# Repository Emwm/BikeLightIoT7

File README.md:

# 🚲 ESP32 Smart Bike Tracker

An ESP32-based smart tracking and monitoring system for bicycles, combining GNSS (GPS) tracking, motion detection, power management, battery monitoring, and LoRa communication to create an intelligent, low-power system for bike security and telemetry.

---

## 📚 Table of Contents

- [Features](#-features)
- [Getting Started](#-getting-started)
- [Power Modes](#-power-modes)
- [GNSS (GPS) Handler](#-gnss-gps-handler)
- [Motion Detector](#-motion-detector)
- [Light Control](#-light-control)
- [LoRa Communication](#-lora-communication)
- [Battery Monitoring](#-battery-monitoring)
- [Inactivity Handling](#-inactivity-handling)
- [Main Loop Overview](#-main-loop-overview)
- [Modules Summary](#-modules-summary)
- [Contributing](#-contributing)
- [License](#-license)

---

## 📦 Features

- Real-time GPS tracking  
- LoRa communication to send bike data remotely  
- Motion detection using an accelerometer  
- Battery monitoring via MAX17048 fuel gauge  
- Smart power management with 3 modes: ACTIVE, PARK, SLEEP  
- Inactivity-based sleep transitions  
- Wake-up on button press or timer  
- Integrated button and light control  

---

## 🛠️ Getting Started

### ✅ Prerequisites

- PlatformIO or Arduino IDE  
- ESP32 board definitions installed  
- Required libraries:  
  - TinyGPS++  
  - Wire  
  - SPI  

### 🚀 Flashing the Firmware

```bash
git clone https://github.com/youruser/esp32-smart-bike-tracker.git
cd esp32-smart-bike-tracker
# Open with Arduino IDE or PlatformIO and upload to your ESP32
```

---

## 🔘 Button Handler

Manages button input from GPIO 33, used to:
- Wake up the system
- Trigger GPS updates
- Toggle power modes

### ⚙️ Configuration

| Constant        | Description                  |
|----------------|------------------------------|
| `BUTTON_PIN_1` | GPIO pin for Button 1 (GPIO33) |

```cpp
#define BUTTON_PIN_1 33
```

### 📦 Variables

```cpp
extern volatile bool button1Pressed;
extern unsigned long lastActivityTime;
```

### 📋 API

| Function            | Description                              |
|---------------------|------------------------------------------|
| `setupButtons()`    | Initializes GPIOs as `INPUT_PULLDOWN`    |
| `checkButtonPresses()` | Resets flags, updates `lastActivityTime` |

---

## 🧠 Power Modes

System behavior varies by mode:

### 🟢 ACTIVE Mode
- Full GPS + LoRa operation
- Motion detection and lighting enabled
- Auto-exit on inactivity

### 🟡 PARK Mode
- Enters light sleep
- Periodic wake via RTC or button
- Ideal for short-term stationary periods

### 🔴 SLEEP Mode
- Enters deep sleep for max power saving
- Wake on button press only
- Best for long inactivity

---

## 🛰 GNSS (GPS) Handler

Handles GPS data using the TinyGPS++ library. Sends the location everytime the mode of the system changes.

### 📋 API

| Method              | Description                                |
|---------------------|--------------------------------------------|
| `begin()`           | Initializes GPS module                     |
| `update()`          | Feeds serial data to TinyGPS++             |
| `isConnected()`     | Checks for GPS fix (≥4 satellites)         |
| `checkLocation()`   | Returns `GPSPosition` with lat/lon         |

### 📍 Example

This flag is used to update the location and send it.

```cpp
if (sendLocationFlag) {
    GPSPosition pos = gnss.checkLocation();
    // Use pos.latitude, pos.longitude
}
```

---

## 🕹️ Motion Detector

Detects bike movement using a 3-axis accelerometer (e.g. ADXL345).

### 📋 API

| Method                  | Description                                  |
|--------------------------|----------------------------------------------|
| `isMoving()`             | Returns `true` if movement detected          |
| `begin()`                | Initializes the sensor                       |
| `MotionDetector(...)`    | Constructor with I2C address and threshold   |

```cpp
MotionDetector motion(0x53); // ADXL345 default I2C address
```

---

## 💡 Light Control

Uses an LDR + MAX7219 LED matrix to control lights.

### ⚙️ Configuration

| Item               | Pin          |
|--------------------|--------------|
| `LDR_PIN`          | Analog Input |
| `LED_LOW_BAT`      | Digital Output |
| `DIN`              | GPIO 14      |
| `CLK`              | GPIO 13      |
| `CS`               | GPIO 12      |

### 📋 API

| Function                      | Description                               |
|-------------------------------|-------------------------------------------|
| `setupLight()`                | Initializes LED matrix                    |
| `controlLight()`              | Enables/disables display based on LDR     |
| `turnLightoff()`              | Manually disables display                 |
| `manageBatteryWarning(float)`| Activates LED when battery < 25%          |

---

## 📡 LoRaWAN Communication

Handles uplink/downlink communication via RN2483 LoRa module using OTAA.

### 🔧 ESP32 to RN2483 Wiring

| Function | ESP32 Pin |
|----------|-----------|
| TX → RN  | GPIO 19   |
| RX ← RN  | GPIO 18   |
| RESET    | GPIO 23   |

### 📋 API

| Function                                  | Description                         |
|-------------------------------------------|-------------------------------------|
| `init_lora()`                             | Initializes LoRaWAN + joins TTN     |
| `send_lora(devMode, battery, lon, lat)`   | Sends telemetry as CSV string       |
| `recieve_lora()`                          | Reads JSON downlink and parses value|

### 📤 Uplink Format (CSV)

```text
1,3.85,12.34,56.78
```

### 📥 Downlink Format

TTN → JSON string in HEX:

```json
{"value": 2}
```

TTN Payload: `7b2276616c7565223a20327d`

Parsed into `int value = 2`.

---

## 🔋 Battery Monitoring

Powered by the MAX17048 fuel gauge.

```cpp
batterypercentage = battery.percent();
```

Low battery warning is triggered by:

```cpp
manageBatteryWarning(batterypercentage);
```

---

## ⏱️ Inactivity & Mode Handling

Automatically switches to `PARK` mode if idle for 60 seconds:

```cpp
if (millis() - lastActivityTime > 60000) {
    // Switch to PARK
}
```

Button interrupt handler toggles modes:

```cpp
void IRAM_ATTR handleInterrupt1();
```

Transitions:
- `ACTIVE → PARK`
- `PARK → SLEEP`

---

## 🔁 Main Loop Structure

```cpp
switch (getCurrentMode()) {
    case ACTIVE:
        // Motion + LoRa
        break;
    case PARK:
        // Light sleep
        break;
    case SLEEP:
        // Deep sleep
        break;
}
```

---

## 🛠 Modules Summary

| Module         | Description                            |
| -------------- | -------------------------------------- |
| powerModes     | Manages sleep states and wake sources  |
| GNSSHandler    | Handles GPS via GNSS                   |
| MotionDetector | Reads accelerometer to detect movement |
| ESP32\_lora    | Sends and receives data via LoRa       |
| MAX17048       | Monitors battery charge level          |
| buttonHandler  | Detects button presses                 |
| lightControl   | Manages LED or light control           |

## Authors

Group 7 in the DTU course 34346 Networking technologies and application development for IoT

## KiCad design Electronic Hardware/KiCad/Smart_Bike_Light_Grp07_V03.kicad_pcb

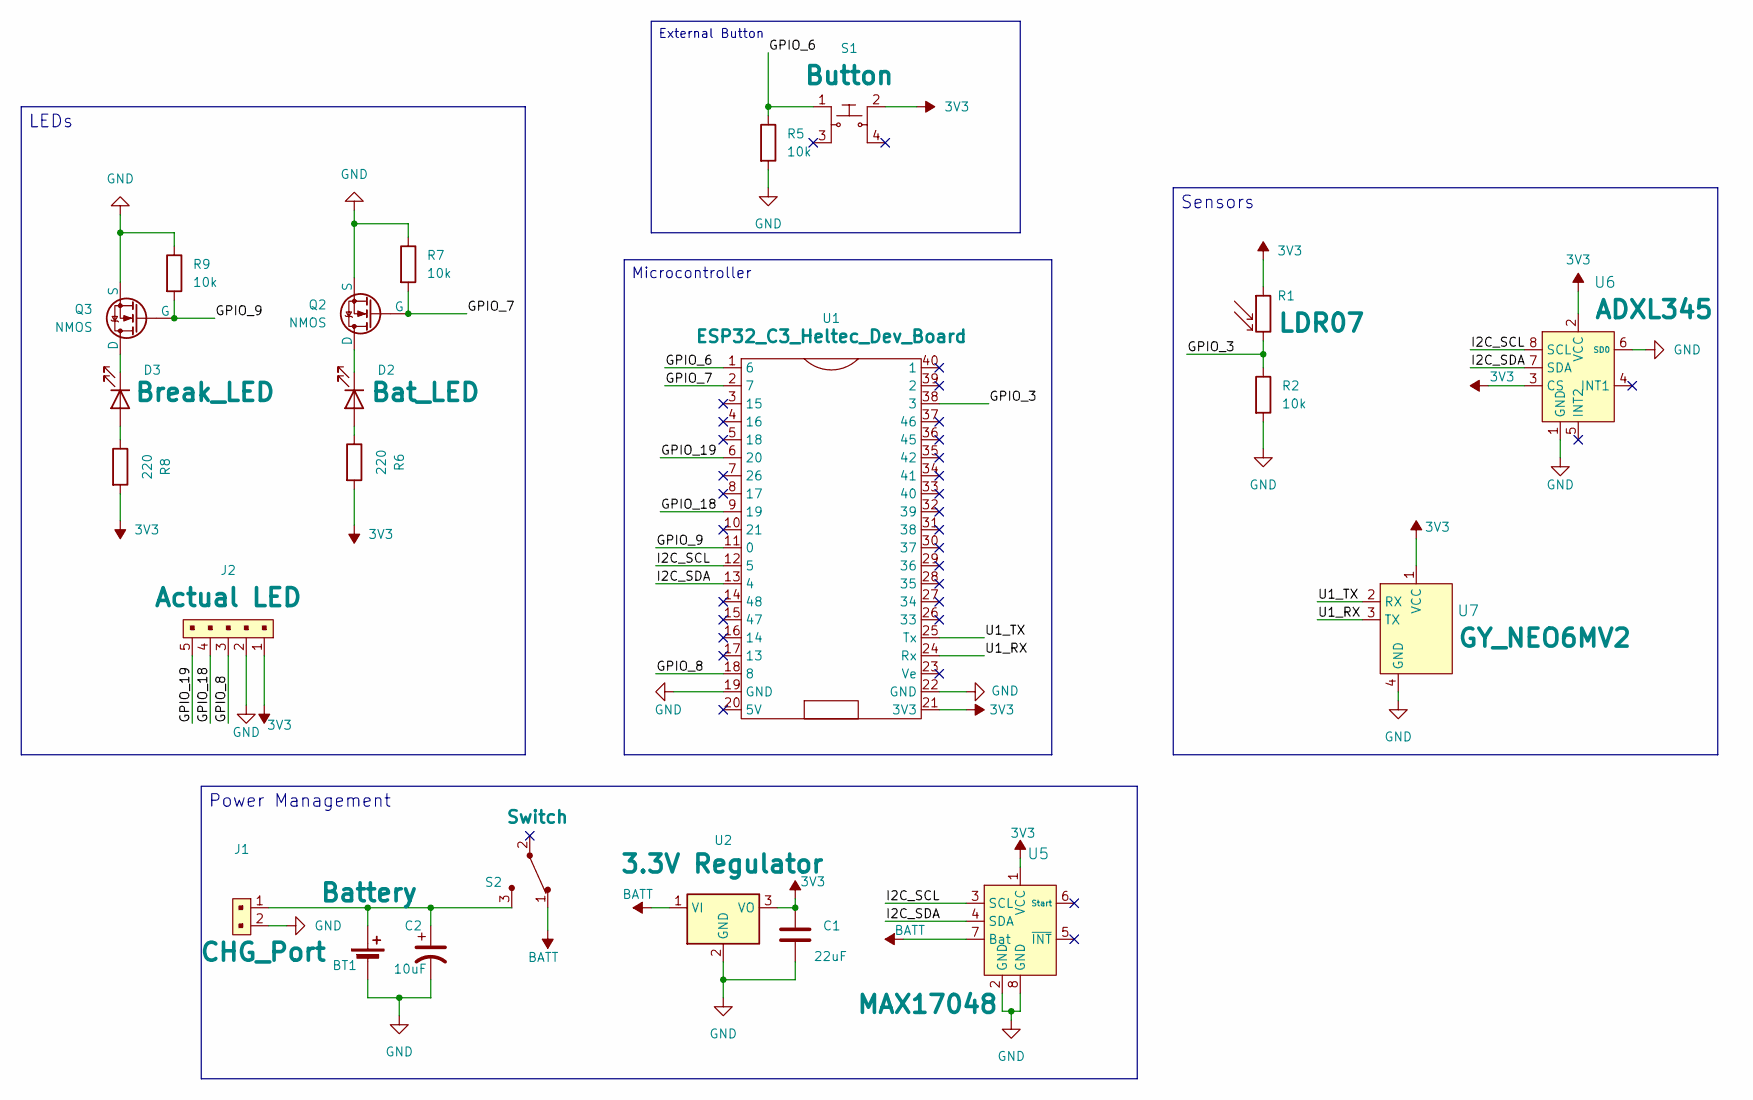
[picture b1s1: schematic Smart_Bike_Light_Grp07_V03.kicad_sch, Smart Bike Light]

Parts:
BT1: Battery; Terminal_Block_D1.3mm_P5mm
C1: 22uF; C_Axial_L3.8mm_D2.6mm_P7.50mm_Horizontal
C2: 10uF; C_Axial_L3.8mm_D2.6mm_P7.50mm_Horizontal
D2: Bat_LED; LED_D3.0mm_Clear
D3: Break_LED; LED_D3.0mm_Clear
J1: CHG_Port; Terminal_Block_D1.3mm_P5mm; MPN 640456-2; Digi-Key_PN A1921-ND
J2: Actual LED; JST_XA_B05B-XASK-1-A_1x05_P2.50mm_Vertical; MPN B5B-XH-A(LF)(SN); Digi-Key_PN 455-2270-ND
Q2, Q3: NMOS; PinHeader_1x3_P2.54_Drill1.1mm
R1: LDR07; R_LDR_5.1x4.3mm_P3.4mm_Vertical
R2, R5, R7, R9: 10k; R_Axial_DIN0204_L3.6mm_D1.6mm_P5.08mm_Horizontal
R6, R8: 220; R_Axial_DIN0204_L3.6mm_D1.6mm_P5.08mm_Horizontal
S1: Button; SW_DIP_SPSTx02_Slide_9.78x7.26mm_W7.62mm_P2.54mm; MPN KS-01Q-01; Digi-Key_PN EG4791-ND
S2: Switch; SW_Slide-03_Wuerth-WS-SLTV_10x2.5x6.4_P2.54mm; MPN EG1218; Digi-Key_PN EG1903-ND
U1: ESP32_C3_Heltec_Dev_Board; DIP-40_W25.4mm
U2: 3.3V Regulator; PinHeader_1x3_P2.54_Drill1.1mm
U5: MAX17048; DIP-8_W7.62mm; MPN MAX44009EDT+T; Digi-Key_PN MAX44009EDT+TCT-ND
U6: ADXL345; DIP-8_W7.62mm; MPN MAX44009EDT+T; Digi-Key_PN MAX44009EDT+TCT-ND
U7: GY_NEO6MV2; DIP-8_W7.62mm; MPN MAX44009EDT+T; Digi-Key_PN MAX44009EDT+TCT-ND

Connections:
-3V3: C1.1, J2.1, R1.1, R6.2, R8.2, S1.2, U1.21 (3V3), U2.3 (VO), U5.1 (VCC), U6.2 (VCC), U6.3 (CS), U7.1 (VCC)
-BATT: S2.1, U2.1 (VI), U5.7 (Bat)
/GPIO_3: R1.2, R2.1, U1.38 (3)
/GPIO_6: R5.1, S1.1, U1.1 (6)
/GPIO_7: Q2.2 (G), R7.2, U1.2 (7)
/GPIO_8: J2.3, U1.18 (8)
/GPIO_9: Q3.2 (G), R9.2, U1.11 (0)
/GPIO_18: J2.4, U1.9 (19)
/GPIO_19: J2.5, U1.6 (20)
/I2C_SCL: U1.12 (5), U5.3 (SCL), U6.8 (SCL)
/I2C_SDA: U1.13 (4), U5.4 (SDA), U6.7 (SDA)
/U1_RX: U1.24 (Rx), U7.3 (TX)
/U1_TX: U1.25 (Tx), U7.2 (RX)
GND: BT1.2 (-), C1.2, C2.2, J1.2, J2.2, Q2.3 (S), Q3.3 (S), R2.2, R5.2, R7.1, R9.1, U1.19 (GND), U1.22 (GND), U2.2 (GND), U5.2 (GND), U5.8 (GND), U6.1 (GND), U6.6 (SD0), U7.4 (GND)
unnamed: BT1.1 (+), C2.1, J1.1, S2.3
unnamed: D2.2 (A), R6.1
unnamed: D2.1 (K), Q2.1 (D)
unnamed: D3.2 (A), R8.1
unnamed: D3.1 (K), Q3.1 (D)

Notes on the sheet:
Power Management
External Button
Microcontroller
LEDs
Sensors

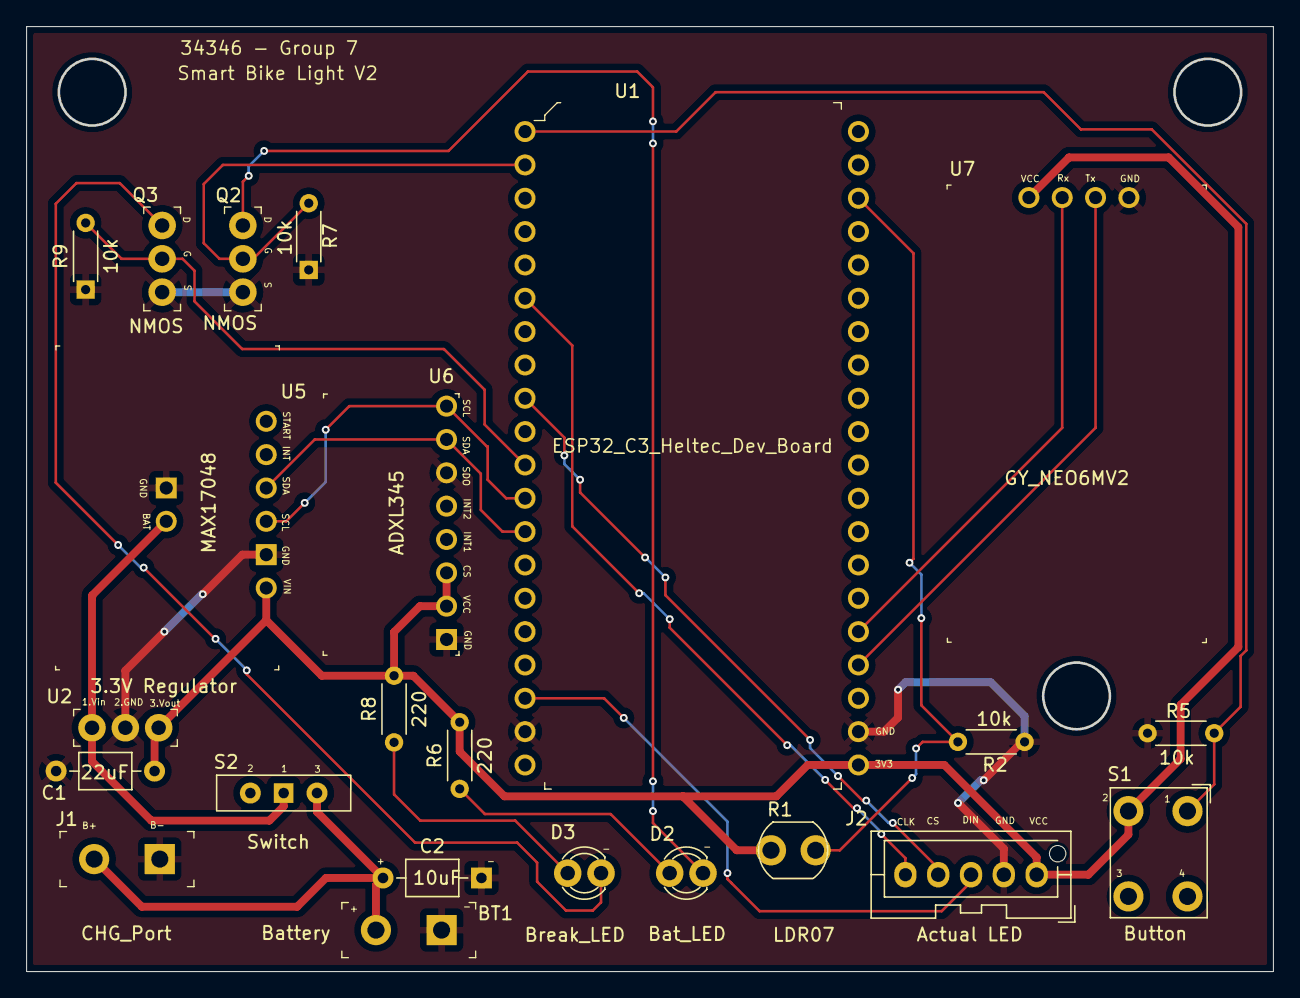
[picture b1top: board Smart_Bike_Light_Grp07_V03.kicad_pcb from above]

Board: 2 copper layers, 95.0 x 72.0 mm, 23 parts (0 on the bottom side), 19 nets.

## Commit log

2025-03-24 Examples Commit
2025-04-03 Sleep Modes and LDR sensor
    I made the sleep modes, the switches between them are not perfect yet, but all of the modes are working as intended. The LDR only turns on the LED, if it is dark and only in the active mode. Also I a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
2025-04-03 just renaming to main file
2025-04-03 Smaller changes of Code
    1. Put the interrupts into the powermodes
    2. Defined the pins in the header to clear a problem
2025-04-03 change the selection of wakeup pins
    Trying to make multiple Pins able to wake up from deep sleep
2025-04-05 Create GNSS.h (Header file)
    Header file for GNSS
2025-04-05 Create GNSS.cpp
    GNSS source file
2025-04-06 Multiple Wakeups ready and correcting some stuff
2025-04-09 Create LoRaWan_v1.ino
    adding the draft of my code for the lorawan
2025-04-24 Updated files for LoraWAN
2025-04-24 update to lora header file
2025-04-27 Added all sensors and the Lorawan code to the project
2025-05-01 Added comments to all the code
2025-05-01 Update LoraWAN_Reese.cpp
    update to lora cpp file
2025-05-01 Updated the code to include batterypercentage
    Just added a function that activates a battery when it is lower then 25% and added the batterychecking
2025-05-08 Update powerModes.cpp
    Just added the fixed code from today, but still have to make the wake up for the light sleep
2025-05-08 Update GNSSHandler.h
    Just to fix the include of the TinyGPSPlus
2025-05-16 ESP32 lorawan
2025-05-16 System working, without lora
2025-05-18 updated lora code
2025-05-18 Close to final version
    Added function for the set of State
2025-05-18 modes updates
2025-05-18 FIxes
2025-05-18 FInished code
2025-05-20 Code final
2025-05-21 Fritzing ESP32 Wroom
2025-05-21 PCB Files Kicad
2025-05-21 Schematic Image
2025-05-21 PCB Layout Image
2025-05-21 Rendered Image PCB
2025-05-21 Gerber File
2025-05-21 All FootPrints
2025-05-24 Update main branch
2025-05-24 Another delete of old files
2025-05-24 Update powerModes.cpp
    Updated code that it also sends location, if the mode is changed by the frontend
2025-05-24 Reorganized
2025-05-24 Electronic Hardware Reorganized
2025-05-24 updated comments
2025-05-25 Additional Reference Documents
2025-05-25 Added Videos
    Videos of the system working
2025-05-25 Payload code
2025-05-25 Cad files
